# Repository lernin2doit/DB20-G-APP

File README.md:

# DB20-G Controller

**Open-source Android app and Bluetooth interface hardware for programming and operating the Radioddity DB20-G GMRS mobile radio.**

> **⚠️ PROJECT STATUS: EARLY DEVELOPMENT — UNTESTED & INCOMPLETE**
>
> This project is in early development and is **not ready for production use**. Both the Android app and the v10 Bluetooth interface hardware exist only as designs at this point — **neither has been fully tested**. The app contains numerous known bugs that still need to be resolved, and to our knowledge **no one has built the hardware yet** for proper end-to-end testing. If you choose to build or use any part of this project, you do so entirely at your own risk. Contributions and testing feedback are welcome — see [CONTRIBUTING.md](CONTRIBUTING.md).

Connect your Android phone to your DB20-G wirelessly over Bluetooth — program channels, manage repeaters, key PTT, and stream live audio, all from a beginner-friendly interface designed around real GMRS community feedback. Your phone stays on its charger while the interface box talks to the radio.

---

## Overview

The DB20-G Controller project is a complete ecosystem for GMRS radio operation:

- **Android App** — Program channels, download/upload radio memory, operate live with PTT, search repeaters, stream audio, and more
- **Bluetooth Interface Box** — Custom open-hardware PCB with ESP32 that wirelessly bridges your phone to the radio (serial + audio + PTT over Bluetooth)
- **ESP32 Firmware** — PlatformIO-based firmware for the interface box (BT SPP, audio streaming, OTA updates)
- **3D-Printable Enclosure** — Parametric OpenSCAD design for housing the interface board

The Radioddity DB20-G is a popular 20-watt GMRS mobile radio, but programming it has been the #1 user complaint across every GMRS community. This project solves that with a 60-second setup wizard, live repeater database, and FCC-compliant validation — no PC required.

## Features

### App

- **60-Second Setup Wizard** — Callsign entry, location permission, radio auto-detect, one-tap programming
- **Channel Management** — Edit all 500 channels with inline validation, frequency/power/tone checking
- **GMRS Channel Templates** — Standard 22, Emergency Kit, Family Pack presets
- **RepeaterBook Integration** — Search repeaters by location, radius, or frequency with local caching
- **Travel Route Planner** — Auto-generate optimal repeater lists for road trips with coverage gap detection
- **Live Operation** — PTT keying, DTMF keypad, channel up/down, RX activity detection, VOX
- **Download/Upload** — Read and write full radio memory over USB serial
- **CHIRP Compatibility** — Import/export CHIRP `.csv` and `.img` files
- **FCC Compliance Tools** — License lookup (ULS API), power limit validation, Part 95 quick reference
- **Emergency Mode** — High-contrast SOS beacon with GPS coordinates, dead-man's switch, emergency net checklist
- **Bluetooth PTT** — Wireless PTT button support (BLE HID) for Sena and generic buttons, plus in-app PTT over Bluetooth SPP
- **Scanner & Priority Scan** — Software-controlled scan lists, priority channel, dual-watch
- **Signal Monitoring** — Audio level meter, RSSI history, spectrum analyzer, range test mode
- **Text Messaging** — AFSK Bell 202 (1200 baud) text-over-radio with GPS position sharing
- **SSTV** — Slow-scan TV image send/receive (Robot36, Martin M1)
- **Android Auto** — Simplified driving-safe UI with voice commands and steering wheel PTT
- **Weather Alerts** — NOAA severe weather notifications by location
- **On-Device Translation** — Real-time radio audio translation (English ↔ Spanish) via ML Kit, fully offline
- **Accessibility** — TalkBack/screen reader support, high-contrast mode, configurable font sizes, haptic feedback
- **QSO Logging** — Contact database, net schedules, ADIF/CSV export
- **Multi-Radio Support** — Manage multiple USB serial radios with profiles and cross-radio channel sync

### Hardware (Bluetooth Interface Box — v10)

```
┌───────────┐  Bluetooth  ┌───────────────────────────┐     RJ-45      ┌──────────┐
│  Android  │◄───────────►│   DB20-G Interface Box    │◄──────────────►│  DB20-G  │
│   Phone   │  SPP serial │                           │ (handset port) │   Radio  │
│           │  SCO audio  │  ESP32-WROOM-32E          │                │          │
│           │             │   → BT serial bridge      │                │          │
│           │             │   → DAC/ADC audio          │                │          │
│           │             │   → PTT / relay control    │                │          │
└───────────┘             └───────────────────────────┘                └──────────┘
```

- **Bluetooth Classic** (SPP + SCO) — phone connects wirelessly; no cable to the phone
- **ESP32-WROOM-32E** — single module replaces the former USB hub, UART bridge, and audio codec
- **9600 baud UART bridge** — BT SPP ↔ ESP32 UART2 for the DB20-G GA-510 programming protocol
- **DAC/ADC audio** — 8 kHz 8-bit mono voice; ESP32 DAC (GPIO25) → radio MIC, radio SPK → ESP32 ADC (GPIO36)
- **Transistor + relay PTT** — GPIO-driven PTT with 3-minute FCC timeout; DPDT relay switches serial ↔ audio mode
- **RJ-45 handset pass-through** — Use the hand mic normally while the interface is connected
- **Audio level matching** — Voltage dividers match ESP32 levels to radio mic/speaker levels
- **LED indicators** — Power/heartbeat (green), PTT (red), audio activity (yellow), BT status (blue)
- **OTA firmware updates** — ESP32 WiFi AP mode with HTTP upload for field-upgradeable firmware
- **NVS config** — Persistent storage for TX/RX gain, PTT timeout, BT name
- **External 5 V power** — Powered from radio handset port, USB adapter, or vehicle lighter. Phone stays on its charger.
- **~30 components, ~$5.28 total BOM** — 2-layer FR4 PCB, hand-solderable

## Screenshots

*Coming soon — contributions welcome!*

## Getting Started

### Prerequisites

- **Android device** running Android 8.0+ (API 26) with Bluetooth
- **Radioddity DB20-G** GMRS mobile radio
- **DB20-G Interface Box** ([build your own](#building-the-interface-box)) — ESP32 Bluetooth interface board
- **RJ-45 patch cable** for connecting the interface box to the radio's handset port
- **5 V power source** — USB adapter, vehicle lighter port, or radio handset port power

### Install the App

#### From Source

```bash
git clone https://github.com/lernin2doit/DB20-G-APP.git
cd DB20-G-APP
./gradlew assembleDebug
```

The APK will be at `app/build/outputs/apk/debug/app-debug.apk`. Transfer it to your Android device and install.

#### Pre-Built APK

Check the [Releases](https://github.com/lernin2doit/DB20-G-APP/releases) page for signed APKs.

### First Use

1. Connect the interface box to your radio's handset port (RJ-45)
2. Power the interface box (5 V via J4 or radio handset port)
3. Open the app and pair with "DB20G-Interface" via Bluetooth
4. Grant Bluetooth permission when prompted
5. The setup wizard will walk you through callsign entry, location, and programming your first channels

> **USB fallback:** The app also supports direct USB serial connection (CP2102, CH340, etc.) for firmware development and bench testing without the Bluetooth interface box.

### Building the Interface Box

Full hardware build documentation is in the [`hardware/`](hardware/) directory:

| Document | Description |
|----------|-------------|
| [hardware/README.md](hardware/README.md) | Overview, block diagram, ESP32 pin assignments |
| [hardware/BOM.md](hardware/BOM.md) | Full bill of materials (~30 components, ~$5.28) |
| [hardware/ASSEMBLY.md](hardware/ASSEMBLY.md) | Step-by-step build guide (5 phases) |
| [hardware/WIRING.md](hardware/WIRING.md) | ESP32 GPIO map, connector pinouts, signal routing |
| [hardware/TROUBLESHOOTING.md](hardware/TROUBLESHOOTING.md) | Common issues and diagnostics |
| [hardware/KICAD-CHANGES.md](hardware/KICAD-CHANGES.md) | v9→v10 schematic change log |

**Tools needed:** Soldering iron with fine tip, solder (0.5 mm recommended), flux, multimeter, USB-UART adapter (for initial ESP32 flashing), 3D printer (for enclosure, optional).

**PCB fabrication:** Upload the KiCad files from `hardware/kicad/` to [JLCPCB](https://jlcpcb.com), [PCBWay](https://www.pcbway.com), or your preferred fab house. Default settings (2-layer, 1.6 mm FR4, HASL) work fine.

**ESP32 firmware:** Flash via J5 UART header using PlatformIO: `cd firmware && pio run --target upload`. See [firmware/README.md](firmware/README.md) for details.

**Enclosure:** Open `hardware/enclosure/DB20G-Enclosure.scad` in [OpenSCAD](https://openscad.org/) and export to STL for 3D printing.

## Building from Source

### Requirements

- **Android Studio** (Hedgehog or newer recommended)
- **JDK 17**
- **Android SDK 34**
- **Gradle 8.7.3** (included via wrapper)

### Build

```bash
# Debug build
./gradlew assembleDebug

# Release build (unsigned)
./gradlew assembleRelease

# Run tests
./gradlew test
```

### Project Structure

```
DB20-G-APP/
├── app/src/main/
│   ├── java/com/db20g/controller/
│   │   ├── ui/             # Activities, fragments, adapters (MVVM)
│   │   ├── protocol/       # DB20-G serial protocol, channel/settings data classes
│   │   ├── serial/         # USB serial communication (CP2102, PL2303, FTDI, CH340)
│   │   ├── transport/      # RadioTransport interface, USB + Bluetooth implementations
│   │   ├── repeater/       # RepeaterBook API, repeater database, callsign ID
│   │   ├── audio/          # DTMF, Morse, VOX, audio routing, Bluetooth audio bridge
│   │   ├── auto/           # Android Auto integration
│   │   ├── bluetooth/      # Bluetooth PTT button support, BT SPP transport
│   │   ├── emergency/      # Emergency mode, SOS beacon
│   │   ├── translation/    # On-device ML Kit translation
│   │   ├── compliance/     # FCC license validation, power limit checking
│   │   └── service/        # Foreground service for persistent radio connection
│   ├── res/                # Layouts, drawables, strings (English + Spanish)
│   └── AndroidManifest.xml
├── firmware/               # ESP32 firmware (PlatformIO + Arduino)
│   ├── src/main.cpp        # BT SPP bridge, audio streaming, OTA, NVS
│   ├── include/pins.h      # GPIO pin definitions
│   ├── include/config.h    # Firmware constants
│   └── platformio.ini      # Build configuration
├── hardware/
│   ├── kicad/              # KiCad 9 schematic (v10 ESP32 Bluetooth design)
│   ├── enclosure/          # OpenSCAD 3D-printable enclosure
│   ├── BOM.md              # Bill of materials
│   ├── ASSEMBLY.md         # Build guide
│   ├── WIRING.md           # Pin mappings, signal routing
│   ├── TROUBLESHOOTING.md  # Diagnostic guide
│   ├── KICAD-CHANGES.md    # v9→v10 schematic change log
│   └── archive/            # Archived v9 USB design files
└── ROADMAP.md              # Feature roadmap (P0–P3 + Bluetooth redesign)
```

## Technology Stack

| Component | Technology |
|-----------|-----------|
| Language | Kotlin 2.0 |
| UI | Material Design 3, ViewPager2, RecyclerView |
| Architecture | MVVM (ViewModel + LiveData + Coroutines) |
| Transport | RadioTransport interface (USB serial + Bluetooth SPP) |
| USB Serial | [usb-serial-for-android](https://github.com/mik3y/usb-serial-for-android) 3.7.3 |
| Location | Google Play Services Location 21.1 |
| Translation | ML Kit Translate 17.0 (on-device) |
| Android Auto | AndroidX Car App 1.4 |
| Min SDK | Android 8.0 (API 26) |
| Target SDK | Android 14 (API 34) |
| Build | Gradle 8.7.3, JDK 17 |
| Firmware | PlatformIO + Arduino framework (ESP32) |
| PCB Design | KiCad 9 |
| Enclosure | OpenSCAD |

## Radio Protocol

The app communicates with the DB20-G using the GA-510 "clone mode" serial protocol:

- **Baud rate:** 9600 8N1
- **Read/write:** 32-byte blocks
- **Total memory:** 7,232 bytes (0x1C40)

| Address Range | Contents |
|---------------|----------|
| `0x0000–0x0800` | Channel data (454 slots × 16 bytes) |
| `0x0C00–0x1400` | Channel names (454 × 16-byte ASCII) |
| `0x1A00–0x1C40` | Radio settings (squelch, VOX, TOT, beep, scan, etc.) |

The clone-mode memory exposes 454 programmable channel slots. The radio's 500-channel capacity includes 30 fixed GMRS channels (1–30), 9 customizable repeater channels (31–39), 454 fully programmable channels (40–493), and 7 NOAA weather channels (494–500). Channels 40–493 can be programmed to any frequency the radio is capable of receiving, including VHF (136–174 MHz) and UHF (400–490 MHz). The 30 GMRS and 7 NOAA channels have fixed frequencies stored in firmware.

Frequencies are stored as 4-byte big-endian BCD. CTCSS/DCS tones use 14-bit indices into standard lookup tables (50 CTCSS tones, 104 DCS codes).

> **Note:** Firmware versions from the manufacturer exist for other jurisdictions that remove the RX-only restrictions, enabling transmit on any programmed frequency. Transmitting outside the GMRS band without an appropriate license (e.g., amateur radio) is illegal under FCC rules and may result in fines or equipment seizure.

## Contributing

Contributions are welcome! Whether it's bug fixes, new features, documentation, hardware improvements, or translations — all help is appreciated.

### How to Contribute

1. **Fork** the repository
2. **Create a branch** for your feature or fix (`git checkout -b feature/my-feature`)
3. **Make your changes** and commit with clear messages
4. **Test** your changes (build the app, verify on a real device if possible)
5. **Open a Pull Request** with a description of what you changed and why

### Areas Where Help Is Needed

- **Testing** on different Android devices and USB adapters
- **Repeater database** contributions (especially regional data)
- **Translations** (Spanish is started; other languages welcome)
- **Hardware testing** and build feedback
- **Documentation** and tutorials
- **UI/UX improvements** and accessibility enhancements

### Code Style

- Kotlin with Android conventions
- MVVM architecture — keep business logic in ViewModels
- Coroutines for async work (no raw threads or AsyncTask)
- Material Design 3 components for UI

### Reporting Issues

Open an issue on GitHub with:
- Android device model and OS version
- USB adapter type (if applicable)
- Steps to reproduce
- Expected vs. actual behavior
- Logcat output (if relevant)

## Roadmap

See [ROADMAP.md](ROADMAP.md) for the full prioritized feature plan. Key areas:

- **P0 (Critical)** — Setup wizard, RepeaterBook integration, validation engine, CHIRP compatibility ✅
- **P1 (High)** — Travel route planner, emergency features, Bluetooth PTT ✅
- **P2 (Medium)** — Scanner, signal monitoring, multi-radio, QSO logging ✅
- **P3 (Nice-to-have)** — Android Auto, SSTV, text messaging, weather, spectrum display ✅
- **BT (v2.0 Redesign)** — ESP32 Bluetooth hardware, firmware, app refactor, docs ✅

## License

This is a dual-licensed open-source project:

- **Software** (Android app, source code) — [MIT License](LICENSE.md)
- **Hardware** (schematics, PCB, enclosure) — [CERN Open Hardware Licence v2 — Permissive (CERN-OHL-P-2.0)](hardware/LICENSE)

See [LICENSE.md](LICENSE.md) for the full software license text.

## Acknowledgments

- **[usb-serial-for-android](https://github.com/mik3y/usb-serial-for-android)** — USB serial driver library by mik3y
- **[RepeaterBook](https://www.repeaterbook.com/)** — GMRS repeater database API
- **[CHIRP](https://chirp.danplanet.com/)** — Cross-platform radio programming tool (file format compatibility)
- **[OpenSCAD](https://openscad.org/)** — Parametric 3D modeling for the enclosure
- **[KiCad](https://www.kicad.org/)** — Open-source PCB design tools
- The **r/gmrs** and **r/amateurradio** communities for feedback, feature requests, and testing

## Disclaimer & Legal Notice

### No Warranty

THIS SOFTWARE AND HARDWARE ARE PROVIDED "AS IS", WITHOUT WARRANTY OF ANY KIND, EXPRESS OR IMPLIED, INCLUDING BUT NOT LIMITED TO THE WARRANTIES OF MERCHANTABILITY, FITNESS FOR A PARTICULAR PURPOSE, AND NONINFRINGEMENT. IN NO EVENT SHALL THE AUTHORS, CONTRIBUTORS, OR COPYRIGHT HOLDERS BE LIABLE FOR ANY CLAIM, DAMAGES, OR OTHER LIABILITY, WHETHER IN AN ACTION OF CONTRACT, TORT, OR OTHERWISE, ARISING FROM, OUT OF, OR IN CONNECTION WITH THE SOFTWARE, HARDWARE DESIGNS, OR THE USE OR OTHER DEALINGS THEREIN.

### Use at Your Own Risk

This project — including the Android application, USB interface hardware designs, PCB schematics, enclosure files, and all associated documentation — is provided for **educational and hobbyist purposes only**. By using, building, or deploying any part of this project, you acknowledge and agree that:

- You do so **entirely at your own risk**.
- The authors and contributors **are not responsible** for any damage to your radio, phone, vehicle, computer, or any other equipment.
- The authors and contributors **are not liable** for any personal injury, property damage, financial loss, or legal consequences resulting from the use or misuse of this project.

### Radio Communications & FCC Compliance

- This project is **not affiliated with, endorsed by, or sponsored by Radioddity, Anytone, or any radio manufacturer**.
- **GMRS operation in the United States requires a valid FCC license** (FCC Part 95, Subpart E). No exam is required, but a license must be obtained before transmitting. Operating without a license is a federal violation subject to fines and enforcement action.
- Users are **solely responsible** for ensuring their radio operation complies with all applicable **federal, state, and local laws and regulations**, including but not limited to FCC Part 95 rules.
- The DB20-G hardware is capable of transmitting outside the GMRS band via third-party firmware modifications — **doing so without the appropriate license (e.g., amateur radio license for amateur bands) is illegal** and may result in FCC enforcement action, including fines up to $100,000+ per violation.
- This software may allow programming of frequencies or settings that are **not legal for transmission** in your jurisdiction. It is **your responsibility** to verify that any programmed configuration complies with applicable law before transmitting.
- The authors **do not encourage, condone, or support** any illegal radio operation, intentional interference, or violation of any telecommunications regulation.

### Distracted Driving & Mobile Device Use

- This application is designed for use with a mobile phone connected to a vehicle-mounted radio. **Many jurisdictions prohibit or restrict the use of mobile devices while driving.**
- **Do not operate this application while driving.** Program your radio while the vehicle is safely parked and stationary.
- The authors and contributors **are not responsible** for any traffic violations, accidents, injuries, or fatalities resulting from the use of this application while operating a motor vehicle.
- You are **solely responsible** for complying with all distracted-driving laws in your jurisdiction.

### Hardware & Electrical Safety

- The USB interface hardware involves custom electronics connected to both your phone and your radio. **Incorrect assembly, wiring, or soldering can damage your devices, create electrical hazards, or cause fire.**
- The hardware designs have **not been professionally certified** for safety (e.g., UL, CE, FCC Part 15 emissions). You build and use them at your own risk.
- The authors **are not responsible** for any damage, injury, or loss caused by building, modifying, or using the hardware.

### Software Bugs & Data Loss

- This application is in **early development** and contains **known and unknown bugs**. It may corrupt radio memory, program incorrect frequencies, cause unexpected radio behavior, or fail during critical operations.
- **Always back up your radio's configuration** before using this software to write to it.
- The authors **are not responsible** for any data loss, radio misconfiguration, or equipment damage caused by software defects.

### Limitation of Liability

TO THE MAXIMUM EXTENT PERMITTED BY APPLICABLE LAW, IN NO EVENT SHALL ANY AUTHOR, CONTRIBUTOR, OR COPYRIGHT HOLDER BE LIABLE FOR ANY DIRECT, INDIRECT, INCIDENTAL, SPECIAL, EXEMPLARY, OR CONSEQUENTIAL DAMAGES (INCLUDING, BUT NOT LIMITED TO, PROCUREMENT OF SUBSTITUTE GOODS OR SERVICES; LOSS OF USE, DATA, OR PROFITS; OR BUSINESS INTERRUPTION) HOWEVER CAUSED AND ON ANY THEORY OF LIABILITY, WHETHER IN CONTRACT, STRICT LIABILITY, OR TORT (INCLUDING NEGLIGENCE OR OTHERWISE) ARISING IN ANY WAY OUT OF THE USE OF THIS SOFTWARE OR HARDWARE, EVEN IF ADVISED OF THE POSSIBILITY OF SUCH DAMAGE.

---

**Built for the GMRS community, by the GMRS community.**

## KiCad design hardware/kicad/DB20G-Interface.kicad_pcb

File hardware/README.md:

# DB20-G Interface Box — Hardware Design (v10 Bluetooth)

> **⚠ UNTESTED DESIGN** — This is a v10 redesign. The PCB has not been
> fabricated or tested yet. Build at your own risk.

Custom wireless interface box that connects an Android phone to a
Radioddity DB20-G GMRS mobile radio over Bluetooth, providing serial
programming control, audio I/O, and PTT keying — **no USB cable to the
phone required**.

## What This Does

```
┌──────────┐  Bluetooth   ┌──────────────────────────┐  RJ-45 + Data   ┌──────────┐
│  Android  │◄────────────►│   DB20-G Interface Box    │◄──────────────►│  DB20-G   │
│   Phone   │  SPP serial  │                           │ (handset port  │   Radio   │
│           │  SCO audio   │  ESP32-WROOM-32E          │  + data port)  │           │
│           │              │   → Bluetooth serial      │                │           │
│           │              │   → Bluetooth audio       │                │           │
│           │              │   → PTT / relay control   │                │           │
└──────────┘              └──────────────────────────┘                  └──────────┘
```

## Features

- **Bluetooth Classic** — phone connects wirelessly (SPP for serial, SCO for audio)
- **ESP32-WROOM-32E** — single module replaces the USB hub + UART + audio codec
- **UART bridge** — 9600 baud 8N1 for DB20-G programming protocol over BT SPP
- **DAC/ADC audio** — ESP32 DAC output → radio MIC, radio SPK → ESP32 ADC
- **Transistor PTT driver** — keys radio via GPIO, controlled from phone
- **DPDT relay** — switches between audio mode and serial/data mode
- **Audio attenuators** — voltage dividers match ESP32 levels to radio
- **RJ-45 handset pass-through** — use the hand mic normally while connected
- **LED indicators** — power/heartbeat, PTT active, audio activity, BT status
- **UART flash header** — J5 (3V3/TX/RX/GND) for ESP32 firmware updates
- **External 5 V power** — powered from USB adapter, vehicle lighter, or radio

## Directory Structure

```
hardware/
├── README.md                           ← You are here (v10 Bluetooth design)
├── BOM.md                              ← Bill of materials (~30 components, ~$5.28)
├── ASSEMBLY.md                         ← Step-by-step build guide (5 phases)
├── WIRING.md                           ← ESP32 GPIO map, connector pinouts, signal routing
├── TROUBLESHOOTING.md                  ← Common issues and solutions
├── KICAD-CHANGES.md                    ← v9→v10 schematic change log
├── kicad/
│   ├── DB20G-Interface-v10.kicad_sch   ← v10 Bluetooth schematic (generated)
│   ├── generate_v10.py                 ← Python schematic generator
│   ├── ERC-v10.json                    ← ERC results (0 errors)
│   └── archive/                        ← Archived v9 KiCad files
├── enclosure/
│   └── DB20G-Enclosure.scad            ← OpenSCAD enclosure
└── archive/                            ← Archived v9 documentation
firmware/
├── platformio.ini                      ← PlatformIO build config
├── include/
│   ├── pins.h                          ← ESP32 GPIO pin definitions
│   └── config.h                        ← Firmware constants
├── src/
│   └── main.cpp                        ← ESP32 firmware (BT SPP bridge)
└── README.md                           ← Firmware documentation
```

## Circuit Overview

### Block Diagram

```
                            ┌────────────────────────────────────────────────┐
                            │          DB20-G Interface Box (v10)            │
                            │                                                │
 [Phone] ◄── Bluetooth ──► │    ┌──────────────────────┐                    │
           SPP serial       │    │  ESP32-WROOM-32E     │                    │
           SCO audio        │    │                      │                    │
                            │    │  UART2 TX (GPIO17) ──┼──► Data Port TX   │
                            │    │  UART2 RX (GPIO16) ◄─┼─── Data Port RX   │
                            │    │                      │                    │
 5V DC ─────────────────────┼──► │  DAC (GPIO25) ───────┼──►[Divider]──► MIC│
                ┌───────┐   │    │  ADC (GPIO36) ◄──────┼──[Divider]◄── SPK │
                │AMS1117│3.3│    │                      │                    │
                │ 3.3V  │──┤    │  GPIO4 ──►[Q1]───────┼──► PTT (pin 4)    │
                └───────┘   │    │  GPIO5 ──►[Q2]───────┼──►[K1 Relay]      │
                            │    │                      │                    │
                            │    │  GPIO18 → LED1 (PWR) │                    │
                            │    │  GPIO19 → LED2 (PTT) │                    │
                            │    │  GPIO21 → LED3 (AUD) │                    │
                            │    │  GPIO22 → LED4 (BT)  │                    │
                            │    └──────────────────────┘                    │
                            │                                                │
                            │    RJ-45 IN ◄────────────► RJ-45 OUT          │
                            │    (Radio)    Pass-through   (Handset)         │
                            └────────────────────────────────────────────────┘
```

### ESP32 Pin Assignment

| GPIO  | Function        | Direction | Net Name      | Notes                       |
|-------|-----------------|-----------|---------------|-----------------------------|
| 25    | DAC Ch1         | Output    | ESP_DAC1      | TX audio to radio MIC       |
| 36    | ADC Ch0 (VP)    | Input     | ESP_ADC0      | RX audio from radio SPK     |
| 16    | UART2 RX        | Input     | ESP_RX2       | Serial data from radio      |
| 17    | UART2 TX        | Output    | ESP_TX2       | Serial data to radio        |
| 4     | Digital out     | Output    | ESP_PTT       | PTT driver (Q1 base via R1) |
| 5     | Digital out     | Output    | ESP_RELAY     | Relay driver (Q2 base via R2) |
| 18    | Digital out     | Output    | ESP_LED1      | Power / heartbeat LED       |
| 19    | Digital out     | Output    | ESP_LED2      | PTT active LED              |
| 21    | Digital out     | Output    | ESP_LED3      | Audio activity LED          |
| 22    | Digital out     | Output    | ESP_LED4      | Bluetooth status LED        |
| EN    | Enable          | Input     | ESP_EN        | Pull-up R11 + C7 RC delay   |
| IO0   | Boot select     | Input     | ESP_IO0       | Pull-up R12 (HIGH = run)    |
| 1     | UART0 TX        | Output    | ESP_TX0       | Debug / flash (J5 pin 2)    |
| 3     | UART0 RX        | Input     | ESP_RX0       | Debug / flash (J5 pin 3)    |

### Radio Connections

**Data Port (rear of DB20-G) — 3.5mm TRS plug:**
| Pin     | Signal       | Direction     |
|---------|-------------|---------------|
| Tip     | TX Data     | Board → Radio |
| Ring    | RX Data     | Radio → Board |
| Sleeve  | Ground      | Common        |

**Handset Port (front of DB20-G) — RJ-45:**
| RJ-45 Pin | Signal          | Interface Box Use          |
|-----------|-----------------|----------------------------|
| 1         | +V Supply       | Pass-through               |
| 2         | Microphone      | ESP32 DAC → Divider → MIC  |
| 3         | Ground          | Common ground              |
| 4         | PTT (active low)| Q1 transistor driver       |
| 5         | Speaker+        | Divider → ESP32 ADC        |
| 6         | Speaker-        | Pass-through               |
| 7         | UP Button       | Pass-through               |
| 8         | DOWN Button     | Pass-through               |

### Command Protocol (Phone ↔ ESP32)

Communication over BT SPP uses a simple framed protocol:

| Command       | ID   | Format                                | Direction      |
|---------------|------|---------------------------------------|----------------|
| Serial data   | 0x01 | `[0x01] [len_hi] [len_lo] [payload…]` | Phone → ESP32  |
| PTT control   | 0x02 | `[0x02] [0x01=press / 0x00=release]`  | Phone → ESP32  |
| Relay mode    | 0x03 | `[0x03] [0x01=serial / 0x00=audio]`   | Phone → ESP32  |

Data from radio → phone flows as raw bytes (no framing).

## Quick Start

1. Order components from [BOM-v10.md](BOM-v10.md)
2. Get PCBs fabricated — upload KiCad Gerber exports to JLCPCB or PCBWay
3. 3D-print the enclosure — export STL from `enclosure/DB20G-Enclosure.scad`
4. Follow [ASSEMBLY.md](ASSEMBLY.md) step-by-step (needs v10 update)
5. Flash ESP32 firmware — see [../firmware/README.md](../firmware/README.md)
6. Wire to radio per [WIRING.md](WIRING.md)
7. If issues, check [TROUBLESHOOTING.md](TROUBLESHOOTING.md)

## Design Decisions

- **ESP32-WROOM-32E** replaces FE1.1s + CP2102N + CM108AH + crystal.  One $2.50
  module provides BT Classic SPP (serial), DAC/ADC (audio), GPIO (PTT/relay),
  and WiFi for future OTA updates. Component count cut nearly in half.
- **Bluetooth Classic** over BLE because SPP gives a UART-like byte stream (no
  MTU fragmentation) and SCO provides a standard audio channel. Android has
  mature BT Classic support.
- **External 5 V power** instead of USB host power — the phone is no longer
  physically connected, so the board needs its own power source. A USB phone
  charger or vehicle lighter adapter works well.
- **DPDT relay (G5V-2)** replaces SPDT — switches both audio channels (MIC +
  SPK) between ESP32 and handset pass-through.
- **2N2222A transistor PTT** retained for zero-latency keying. The relay
  provides a backup.
- **RJ-45 pass-through** so the hand mic works normally when the relay is in
  handset mode.

## License

Hardware designs are provided under the MIT License. See the project root
[LICENSE](../LICENSE) file.

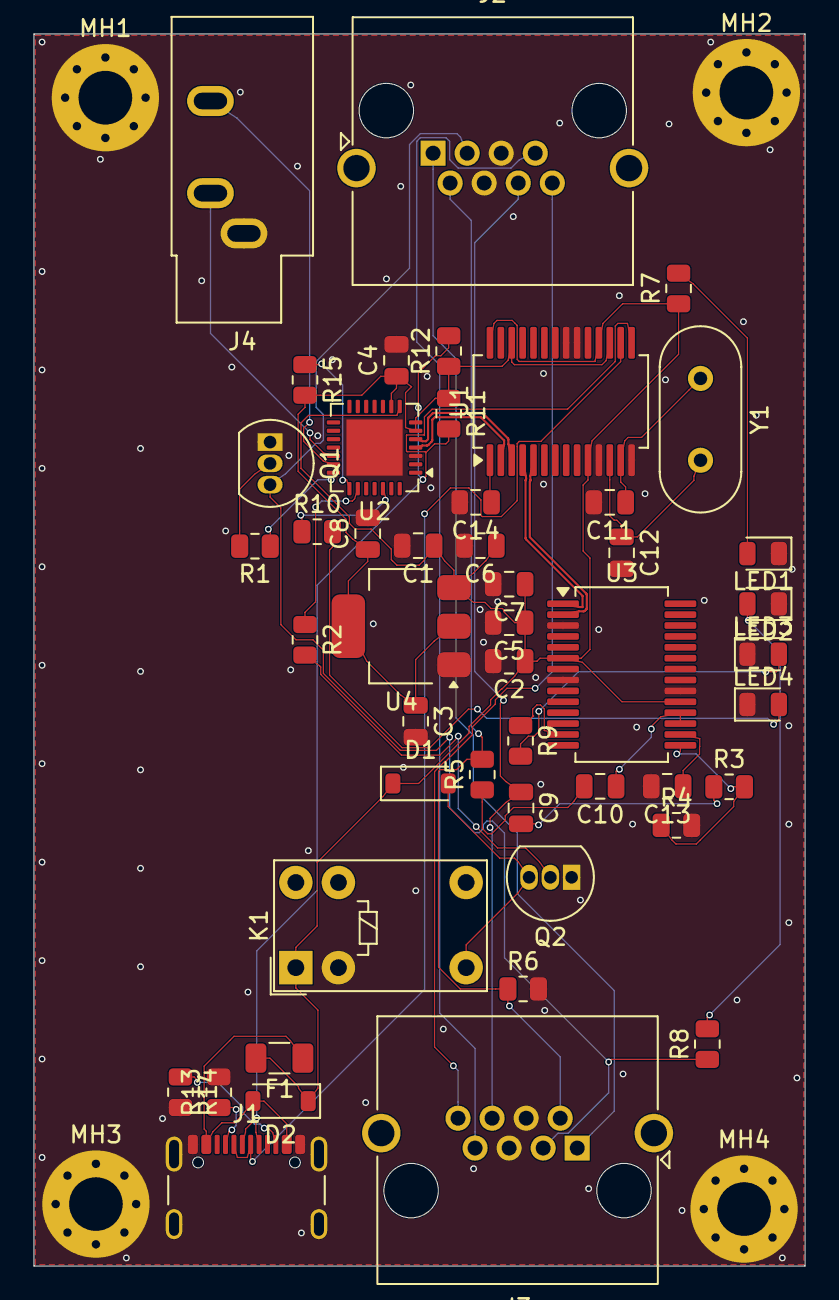
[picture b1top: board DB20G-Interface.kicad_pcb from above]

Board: 2 copper layers, 46.0 x 73.5 mm, 52 parts (0 on the bottom side), 22 nets.

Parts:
C1, C3, C5, C14: 100nF; C_0805_2012Metric
C2, C4, C6, C7: 10µF; C_0805_2012Metric
C8: 22µF; C_0805_2012Metric
C9, C10: 1µF; C_0805_2012Metric
C11, C12: 22pF; C_0805_2012Metric
C13: 4.7µF; C_0805_2012Metric
D1: 1N4148; D_SOD-123
D2: 1N5819; D_SOD-123
F1: 500mA; Fuse_1206_3216Metric
J1: USB-C; USB_C_Receptacle_GCT_USB4105-xx-A_16P_TopMnt_Horizontal
J2: RADIO; RJ45_Amphenol_RJHSE5380
J3: HANDSET; RJ45_Amphenol_RJHSE5380
J4: DATA; Jack_3.5mm_CUI_SJ1-3533NG_Horizontal
K1: G5V-1-DC5; Relay_SPDT_Omron_G5V-1
LED1: Green; LED_0805_2012Metric
LED2: Red; LED_0805_2012Metric
LED3: Yellow; LED_0805_2012Metric
LED4: Blue; LED_0805_2012Metric
MH1, MH2, MH3, MH4: M3; MountingHole_3.2mm_M3_Pad_Via
Q1, Q2: 2N2222A; TO-92_Inline
R1, R2, R3, R5, R15: 10kΩ; R_0805_2012Metric
R4, R6: 1kΩ; R_0805_2012Metric
R7, R8, R9, R10: 330Ω; R_0805_2012Metric
R11: 4.7kΩ; R_0805_2012Metric
R12: 1.5kΩ; R_0805_2012Metric
R13, R14: 5.1kΩ; R_0805_2012Metric
U1: FE1.1s; SSOP-28_5.3x10.2mm_P0.65mm
U2: CP2102N; QFN-28-1EP_5x5mm_P0.5mm_EP3.35x3.35mm
U3: CM108AH; SSOP-28_5.3x10.2mm_P0.65mm
U4: AMS1117-3.3; SOT-223-3_TabPin2
Y1: 12MHz; Crystal_HC49-U_Vertical

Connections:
+3V3: C1.1, C1.2, C2.1, C2.2, C3.1, C3.2, C4.1, C4.2, C5.1, C5.2, C6.1, C6.2, C7.1, C7.2, C8.1, C8.2, C11.2, C12.2, C13.2, C14.2, D1.1 (K), D2.1 (K), F1.2, J1.A1 (GND), J1.A5 (CC1), J1.S1 (SHIELD), J3.4, J3.5, K1.1 (Coil+), K1.2 (Coil-), LED1.1 (K), LED1.2 (A), LED2.1 (K), LED2.2 (A), LED3.1 (K), LED3.2 (A), LED4.1 (K), LED4.2 (A), MH1.1, MH2.1, MH3.1, MH4.1, Q1.1 (C), Q1.2 (B), Q2.1 (C), R1.2, R4.2, R6.2, R7.1, R7.2, R8.2, R9.2, R10.2, R11.1, R12.1, R13.1, R13.2, R14.2, R15.2, U1.10 (VCC5), U1.11 (GND2), U1.14 (GND), U1.17 (VCC33), U1.18 (VCC5_2), U1.20 (GND3), U1.21 (GND4), U1.26 (VCC33_2), U1.28 (VCC5_3), U2.1 (GND), U2.2 (OUT), U2.3 (IN), U3.3 (GND), U3.6 (VDD), U3.7 (REGIN), U3.8 (VBUS), U3.9 (~RST), U3.19 (TXD), U3.20 (RXD), U4.1 (D+), U4.2 (D-), U4.3 (GND)
/CC2: J1.B5 (CC2), R14.1
/CTS: R9.1, R15.1, U3.22 (CTS)
/DTR: R2.1, U3.23 (DTR)
/HS_VCC: J2.1 (TIP), J3.1
/HUB_P1_D+: U1.2 (DD1+), U3.4 (D+)
/HUB_P1_D-: U1.3 (DD1-), U3.5 (D-)
/TX_LED: R10.1, U3.26 (TX_LED)
/USB_D-: J1.A7 (D-), U1.16 (UD-)
/VDD18: C14.1, U1.1 (VDD18)
/XO: C12.1, U1.12 (XO), Y1.2
CM108_MIC: R3.2, R4.1
Net-C9-R3: C9.2, R3.1
Net-C10-R5: C10.2, R5.1
Net-R2-Q2: J1.A6 (D+), Q2.2 (B), R2.2, R11.2, R12.2, U1.15 (UD+)
PTT: J2.3 (SLEEVE), J3.3, Q1.3 (E), R8.1
RADIO_MIC: J2.2 (RING), J3.2, R5.2, R6.1
RADIO_SPK: C9.1, J3.6
RELAY_DRV: D1.2 (A), K1.5 (NC), Q2.3 (E)
RTS: R1.1, U3.21 (RTS)
VBUS: D2.2 (A), F1.1, J1.A4 (VBUS)
XI: C11.1, U1.13 (XI), Y1.1

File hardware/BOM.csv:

"Designator","Comment","Footprint","Quantity","LCSC Part Number"
"U1","FE1.1s","SSOP-28","1","C2688765"
"U2","CP2102N-A01-GQFN28","QFN-28","1","C6568"
"U3","CM108AH","SSOP-28","1","C7509"
"U4","AMS1117-3.3","SOT-223","1","C6186"
"Q1","2N2222A","TO-92","1","C118536"
"Q2","2N2222A","TO-92","1","C118536"
"D1","1N4148","DO-35","1","C14516"
"D2","1N5819","DO-41","1","C2480"
"J1","USB-C Receptacle","SMD","1","C168688"
"J2","RJ-45 Jack","TH","1","C386756"
"J3","RJ-45 Jack","TH","1","C386756"
"J4","3.5mm TRS Jack","TH","1","C145822"
"J5","Pin Header 2x5","TH","1",""
"K1","G5V-1-DC5","TH","1","C100024"
"Y1","12MHz Crystal","HC-49S","1","C32180"
"R1","10k","0805","1",""
"R2","10k","0805","1",""
"R3","10k","0805","1",""
"R4","1k","0805","1",""
"R5","10k","0805","1",""
"R6","1k","0805","1",""
"R7","330","0805","1",""
"R8","330","0805","1",""
"R9","330","0805","1",""
"R10","330","0805","1",""
"R11","4.7k","0805","1",""
"R12","1.5k","0805","1",""
"R13","5.1k","0805","1",""
"R14","5.1k","0805","1",""
"R15","10k","0805","1",""
"C1","100nF","0805","1",""
"C2","10uF","0805","1",""
"C3","100nF","0805","1",""
"C4","10uF","0805","1",""
"C5","100nF","0805","1",""
"C6","10uF","0805","1",""
"C7","10uF","0805","1",""
"C8","22uF","0805","1",""
"C9","1uF","0805","1",""
"C10","1uF","0805","1",""
"C11","22pF","0805","1",""
"C12","22pF","0805","1",""
"C13","4.7uF","0805","1",""
"C14","100nF","0805","1",""
"LED1","Green","0805","1","C2297"
"LED2","Red","0805","1","C84256"
"LED3","Yellow","0805","1","C2296"
"LED4","Blue","0805","1","C72041"
"F1","500mA Polyfuse","1206","1","C70069"

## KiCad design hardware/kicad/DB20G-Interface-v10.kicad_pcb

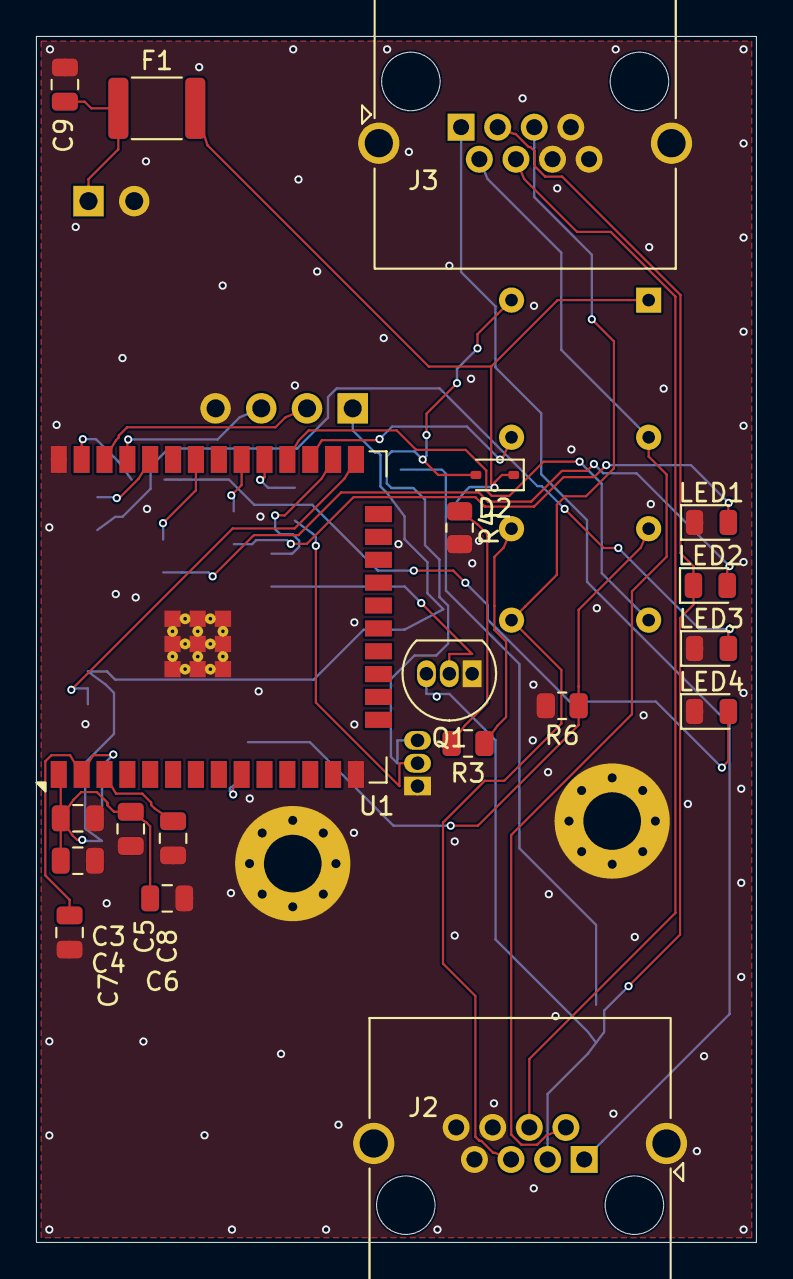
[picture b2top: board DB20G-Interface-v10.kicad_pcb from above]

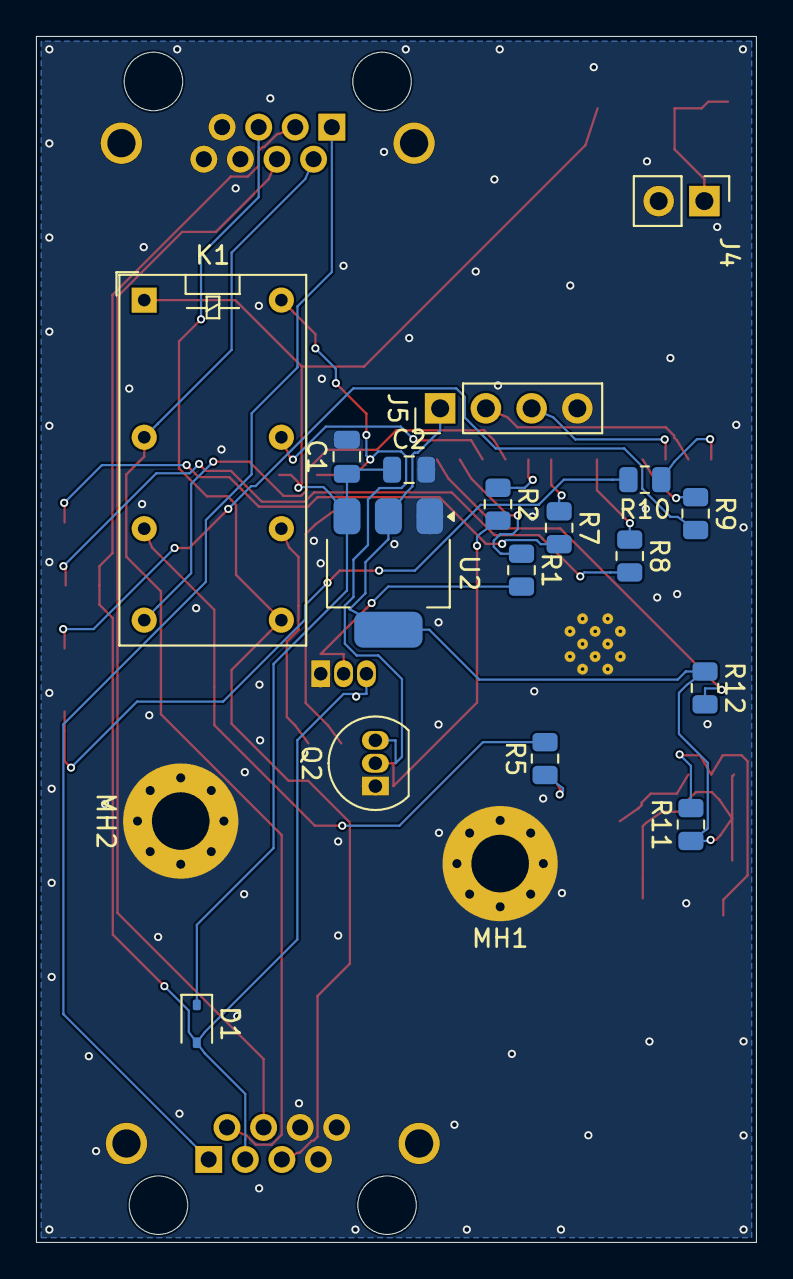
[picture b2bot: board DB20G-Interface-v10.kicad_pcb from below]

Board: 2 copper layers, 40.0 x 67.0 mm, 39 parts (19 on the bottom side), 33 nets.

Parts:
C1, C3, C5, C7, C8, C9: 100nF; C_0805_2012Metric
C2, C4: 10uF; C_0805_2012Metric
C6: 22uF; C_0805_2012Metric
D1: 1N4148; D_SOD-323
D2: 1N5819; D_SOD-323
F1: 500mA; Fuse_1812_4532Metric
J2: RADIO; RJ45_Amphenol_RJHSE5380
J3: HANDSET; RJ45_Amphenol_RJHSE5380
J4: EXT_PWR; PinHeader_1x02_P2.54mm_Vertical
J5: UART_FLASH; PinHeader_1x04_P2.54mm_Vertical
K1: G5V-2-DC5; Relay_DPDT_Omron_G5V-2
LED1: Green; LED_0805_2012Metric
LED2: Red; LED_0805_2012Metric
LED3: Yellow; LED_0805_2012Metric
LED4: Blue; LED_0805_2012Metric
MH1, MH2: M3; MountingHole_3.2mm_M3_Pad_Via
Q1, Q2: 2N2222A; TO-92_Inline
R1, R2, R3, R5, R11, R12: 10k; R_0805_2012Metric
R4, R6: 4.7k; R_0805_2012Metric
R7, R8, R9, R10: 220; R_0805_2012Metric
U1: ESP32-WROOM-32E
U2: AMS1117-3.3; SOT-223-3_TabPin2

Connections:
+3.3V: C3.1, C4.1, C5.1, C6.1, J5.1, R11.1, R12.1, U1.1, U2.2
+5V: C1.1, C2.1, D1.1, D2.1, F1.2, K1.1, U2.3
+5V_EXT: C9.1, F1.1, J4.1
AUDIO_RX: K1.11, R3.1
AUDIO_RX_DIV: R3.2, R4.1
AUDIO_TX_DIV: K1.6, R5.2, R6.1
ESP_ADC0: C8.1, U1.3
ESP_DAC1: R5.1, U1.9
ESP_EN: C7.1, R11.2, U1.2
ESP_IO0: R12.2, U1.25
ESP_LED1: R7.1, U1.30
ESP_LED2: R8.1, U1.32
ESP_LED3: R9.1, U1.34
ESP_LED4: R10.1, U1.37
ESP_PTT: R1.1, U1.26
ESP_RELAY: R2.1, U1.29
ESP_RX0: J5.3, U1.35
ESP_RX2: K1.13, U1.27
ESP_TX0: J5.2, U1.36
ESP_TX2: K1.8, U1.28
GND: C1.2, C2.2, C3.2, C4.2, C5.2, C6.2, C7.2, C8.2, C9.2, J2.6, J2.7, J2.8, J2.SH, J3.6, J3.7, J3.8, J3.SH, J4.2, J5.4, LED1.1, LED3.1, LED4.1, MH1.1, MH2.1, Q1.1, Q2.1, R4.2, R6.2, U1.14, U1.38, U1.39, U2.1
LED1_R: LED1.2, R7.2
LED2_R: LED2.2, R8.2
LED3_R: LED3.2, R9.2
LED4_R: LED4.2, R10.2
PTT_BASE: Q1.2, R1.2
PTT_OUT: D1.2, J2.3, J3.3, LED2.1, Q1.3
RADIO_MIC: J2.2, J3.2, K1.4
RADIO_SPK: J2.5, J3.5, K1.9
RADIO_SQL: J2.4, J3.4
RELAY_BASE: Q2.2, R2.2
RELAY_COIL_LO: D2.2, K1.16, Q2.3
RJ45_P1: J2.1, J3.1

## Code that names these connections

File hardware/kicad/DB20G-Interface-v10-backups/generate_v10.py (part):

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
    # ---- RJ-45 RADIO (to DB20-G handset port) ----
    "J2": {
        "1": "RJ45_P1",             # Radio pin 1 (pass-through)
        "2": "RADIO_MIC",           # MIC/TX to radio ← K1 P1_COM
        "3": "PTT_OUT",             # PTT ← Q1 collector
        "4": "RADIO_SQL",           # Squelch detect (pass-through)
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
    # ---- Resistors ----
    # R1-R2: Transistor base resistors (ESP32 GPIO is 3.3V, 10k gives ~0.33mA base)
    "R1":  {"1": "ESP_PTT",     "2": "PTT_BASE"},       # 10k: GPIO4 → Q1 base
    "R2":  {"1": "ESP_RELAY",   "2": "RELAY_BASE"},     # 10k: GPIO5 → Q2 base
    # R3-R6: Audio dividers (adjusted for ESP32 ADC 0-3.3V range)
    "R3":  {"1": "AUDIO_RX",    "2": "AUDIO_RX_DIV"},   # 10k: RX divider upper
    "R4":  {"1": "AUDIO_RX_DIV","2": "GND"},             # 4.7k: RX divider lower (gives ~1.1V from 3.3V)
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    "R9":  {"1": "ESP_LED3",  "2": "LED3_R"},           # 220Ω: LED3 (Audio)
    "R10": {"1": "ESP_LED4",  "2": "LED4_R"},           # 220Ω: LED4 (BT Status)
    # R11-R12: ESP32 boot/enable pull-ups
    "R11": {"1": "+3.3V",    "2": "ESP_EN"},            # 10k: EN pin pull-up
    "R12": {"1": "+3.3V",    "2": "ESP_IO0"},           # 10k: GPIO0 pull-up (run mode)

    # ---- LEDs (pin 1=Cathode, pin 2=Anode) ----
    "LED1": {"1": "GND",       "2": "LED1_R"},   # Power (Green)
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    "C4":  {"1": "+3.3V",   "2": "GND"},   # 10uF:  AMS1117 output bulk
    "C5":  {"1": "+3.3V",   "2": "GND"},   # 100nF: ESP32 3V3 bypass (close to pin 1)
    "C6":  {"1": "+3.3V",   "2": "GND"},   # 22uF:  ESP32 3V3 bulk decoupling
    "C7":  {"1": "ESP_EN",  "2": "GND"},   # 100nF: EN pin RC delay for stable boot
    "C8":  {"1": "ESP_ADC0","2": "GND"},   # 100nF: ADC input filtering
    "C9":  {"1": "+5V_EXT", "2": "GND"},   # 100nF: Input power filtering

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
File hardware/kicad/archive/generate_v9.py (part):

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        (pin input line (at 12.7 -5.08 180) (length 2.54) (name "GPIO.3" (effects (font (size 1.0 1.0)))) (number "18" (effects (font (size 1.0 1.0)))))
        (pin output line (at 12.7 -2.54 180) (length 2.54) (name "TXD" (effects (font (size 1.0 1.0)))) (number "19" (effects (font (size 1.0 1.0)))))
        (pin input line (at 12.7 0 180) (length 2.54) (name "RXD" (effects (font (size 1.0 1.0)))) (number "20" (effects (font (size 1.0 1.0)))))
        (pin output line (at 12.7 2.54 180) (length 2.54) (name "RTS" (effects (font (size 1.0 1.0)))) (number "21" (effects (font (size 1.0 1.0)))))
        (pin input line (at 12.7 5.08 180) (length 2.54) (name "CTS" (effects (font (size 1.0 1.0)))) (number "22" (effects (font (size 1.0 1.0)))))
        (pin output line (at 12.7 7.62 180) (length 2.54) (name "DTR" (effects (font (size 1.0 1.0)))) (number "23" (effects (font (size 1.0 1.0)))))
        (pin input line (at 12.7 10.16 180) (length 2.54) (name "DSR" (effects (font (size 1.0 1.0)))) (number "24" (effects (font (size 1.0 1.0)))))
        (pin input line (at 12.7 12.7 180) (length 2.54) (name "DCD" (effects (font (size 1.0 1.0)))) (number "25" (effects (font (size 1.0 1.0)))))
        (pin input line (at 12.7 15.24 180) (length 2.54) (name "RI" (effects (font (size 1.0 1.0)))) (number "26" (effects (font (size 1.0 1.0)))))
        (pin output line (at 12.7 17.78 180) (length 2.54) (name "TX_LED" (effects (font (size 1.0 1.0)))) (number "27" (effects (font (size 1.0 1.0)))))
        (pin output line (at 12.7 20.32 180) (length 2.54) (name "RX_LED" (effects (font (size 1.0 1.0)))) (number "28" (effects (font (size 1.0 1.0)))))
      )
      (embedded_fonts no)
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
    # ---- RJ-45 RADIO (to DB20-G handset port) ----
    "J2": {
        "1": "RJ45_P1",                        # Radio pin 1 (pass-through)
        "2": "RADIO_MIC",                      # MIC/TX to radio ← K1 P1_COM
        "3": "PTT_OUT",                        # PTT ← Q1 collector
        "4": "RADIO_SQL",                      # Squelch detect (pass-through)
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    # ---- LEDs (pin 1=Cathode, pin 2=Anode) ----
    "LED1": {"1": "GND",       "2": "LED1_R"},   # Power (Green): +5V→R7→LED1→GND
    "LED2": {"1": "PTT_OUT",   "2": "LED2_R"},   # PTT (Red): +5V→R8→LED2→PTT_OUT
    "LED3": {"1": "CM_GPIO4",  "2": "LED3_R"},   # Audio (Yellow): +3.3V→R9→LED3→GPIO4
    "LED4": {"1": "CP_TXLED",  "2": "LED4_R"},   # Serial (Blue): +3.3V→R10→LED4→TX_LED

    # ---- Capacitors (pin 1=top, pin 2=bottom/GND) ----
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
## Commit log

2026-03-16 Add .gitignore file to exclude build artifacts and IDE configurations
2026-03-17 Refactor code structure for improved readability and maintainability
2026-03-19 Revision to the Hardware interface
2026-03-20 Refactor DB20-G Enclosure Design and Update Documentation
    - Updated enclosure design for DB20-G Interface Box to accommodate revised PCB dimensions and connector layout.
    - Enhanced assembly instructions and print settings for improved user guidance.
    - Added snap-fit detent features for lid retention.
    - Introduced new mounting hole positions based on KiCad measurements.
    - Improved ventilation slot design and added strain-relief slot for USB-C cable.
    - Created CONTRIBUTING.md to outline contribution guidelines for the project.
2026-03-23 Update to architecture, and transition to BLE

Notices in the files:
hardware/kicad/DB20G-Interface.kicad_pcb:
License: CERN-OHL-P-2.0
